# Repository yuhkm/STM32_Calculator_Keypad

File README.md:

# STM32_Calculator_Keypad
STM32 Based USB Keypad and Calculator Project  
<br>

## Overview
Development Period : 2024.08 ~ 2024.11
<br>
### HW
- MCU : STM32F401RET6  
- Displsy : ST7789 1.9" TFT LCD  
- Battery : Li-Po 500mAh 3.7V  
- Interface: USB (for keypad mode and charging)
- Switches: Cherry MX compatible mechanical switches  
  ( Kailh hot-swap sockets )
-  
-  
 
### SW
- Maximum expression length: 70 characters
- Calculator supported Operations  
  Basic arithmetic : +, -, ×, ÷  
  Parentheses : (), {}, []  
  Trigonometric functions : sin, cos, tan  
  Planned support for : asin, acos, atan, log, ln   
-  
-  

## Key Features
- Mode 0 : Calculator
- Mode 1 : USB Keypad  
<br>

| USB C | Power S/W | Mode S/W | Function            | Power source             |
|:-----:|:----------:|:--------:|--------------------|--------------------------|
|   0   |     0      |    X     | Power off          | -                        |
|   0   |     1      |    0     | Calculator mode    | Battery                  |
|   0   |     1      |    1     | -                  | -                        |
|   1   |     0      |    X     | Power off          | Battery charge           |
|   1   |     1      |    0     | Calculator mode    | USB + Battery charge     |
|   1   |     1      |    1     | USB Keypad mode    | USB + Battery charge     |

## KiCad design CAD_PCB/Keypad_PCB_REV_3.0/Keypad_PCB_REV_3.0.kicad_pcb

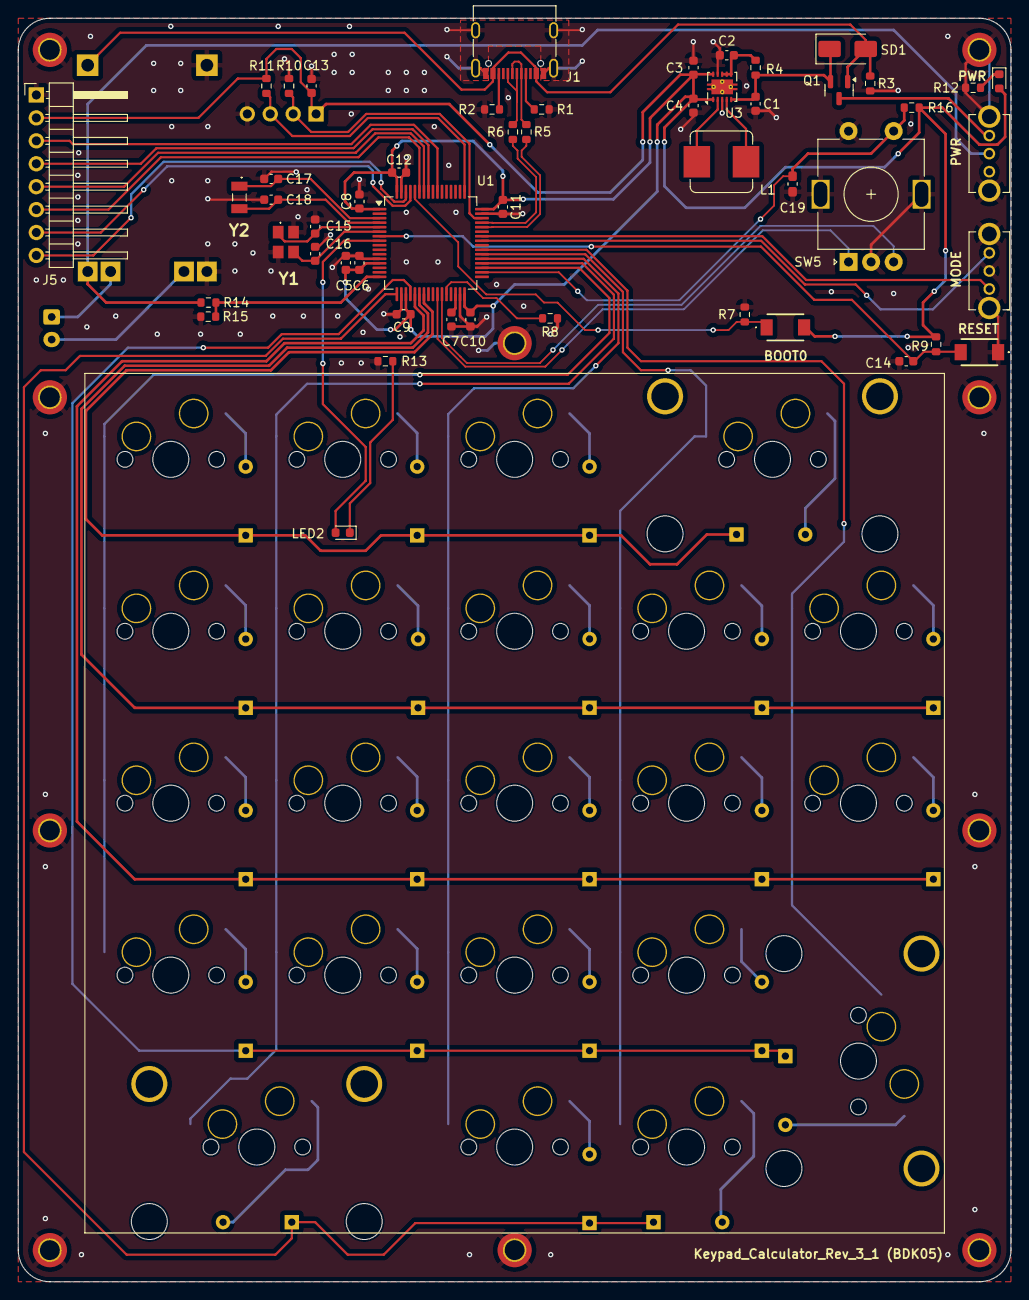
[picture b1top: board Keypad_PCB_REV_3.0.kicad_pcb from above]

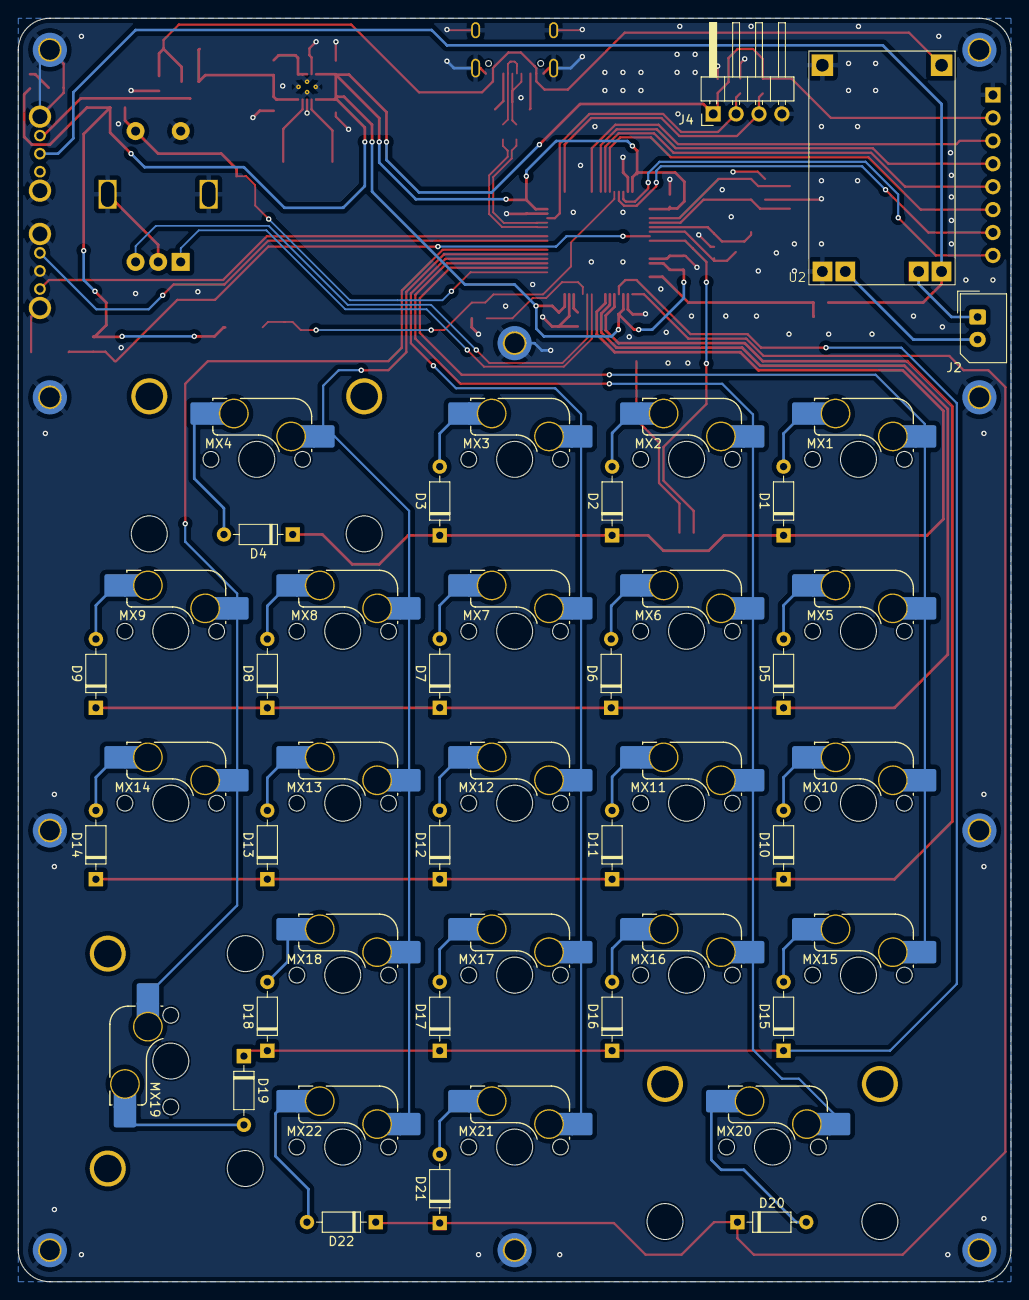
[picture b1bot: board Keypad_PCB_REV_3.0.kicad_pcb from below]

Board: 2 copper layers, 110.0 x 140.0 mm, 111 parts (47 on the bottom side), 74 nets.

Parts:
C1, C3, C4: 10uF(0603); C_0603_1608Metric
C2, C5, C9, C10, C11, C12, C13, C14: 100nF(0603); C_0603_1608Metric
C6, C8: 1uF(0603); C_0603_1608Metric
C7: 4.7uF(0603); C_0603_1608Metric
C15, C16: 18pF(0603); C_0603_1608Metric
C17, C18: 15pF(0603); C_0603_1608Metric
C19: NU(0603); C_0603_1608Metric_Pad1.08x0.95mm_HandSolder
D1, D2, D3, D4, D5, D6, D7, D8, D9, D10, D11, D12, D13, D14, D15, D16, D17, D18, D19, D20, D21, D22: 1N4148; D_DO-35_SOD27_P7.62mm_Horizontal
H1, H2, H3, H4, H5, H6, H7, H8, H9, H10: Pad; MountingHole_2.2mm_M2_DIN965_Pad_TopBottom
J1: USB_C_Receptacle_USB2.0_16P; USB_C_Receptacle_G-Switch_GT-USB-7010ASV
J2: Conn_01x02_Socket; Molex_SPOX_5267-02A_1x02_P2.50mm_Vertical
J4: Conn_01x04_Pin; PinHeader_1x04_P2.54mm_Horizontal
J5: Conn_01x08_Pin; PinHeader_1x08_P2.54mm_Horizontal
L1: 2.2uH; L_Bourns_SRP7028A_7.3x6.6mm
LED1, LED2: LED; LED_0603_1608Metric
MX1, MX2, MX3, MX4, MX5, MX6, MX7, MX8, MX9, MX10, MX11, MX12, MX13, MX14, MX15, MX16, MX17, MX18, MX19, MX20, MX21, MX22: MX_SW_HS; SW_MX_HS_CPG151101S11_1u
Q1: AO3401A; SOT-23
R1, R2: 5.1kR(0603); R_0603_1608Metric
R3, R7, R8, R9, R10, R11, R16: 10kR(0603); R_0603_1608Metric
R4: 100R(0603); R_0603_1608Metric
R5, R6: 22R(0603); R_0603_1608Metric
R12, R13: 1kR(0603); R_0603_1608Metric
R14: 30kR(0603); R_0603_1608Metric
R15: 7.5kR(0603); R_0603_1608Metric
SD1: SS14; D_SMA
ST9, ST19, ST20: MX_stab; STAB_MX_P_2u
SW1, SW2: SK-12D02-VG7; SK12D02VG7
SW3, SW4: TS-1088-AR02016; TS1088AR02016
SW5: RotaryEncoder_Switch_MP; RotaryEncoder_Alps_EC11E-Switch_Vertical_H20mm
U1: STM32F401RETx; LQFP-64_10x10mm_P0.5mm
U2: TP4056_Module
U3: TPS63001; Texas_DRC0010J_ThermalVias
Y1: X322525MOB4SI
Y2: Q13FC1350000400

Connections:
+3.3V: C3.1, C4.1, C5.1, C6.1, C8.1, C9.1, C10.1, C11.1, C12.1, C13.1, J4.1, J5.2, LED1.2 (A), R9.2, R11.1, R16.2, SW4.2 (NO), U1.1 (VBAT), U1.13 (VREF+), U1.19 (VDD), U1.32 (VDD), U1.48 (VDD), U1.64 (VDD), U3.1 (VOUT), U3.10 (FB)
/Stm32/D+: R6.1, U1.45 (PA12)
/Stm32/D-: R5.1, U1.44 (PA11)
BAT_ADC: R14.1, R15.2, U1.16 (PA2)
BLK: J5.8, U1.62 (PB9)
BOOT0: R7.1, SW4.1 (COM), U1.60 (BOOT0)
BOOT1: R8.1, U1.28 (PB2)
BOUT+: R14.2, SW1.2, U2.3 (Bout+)
COL0: MX1.1, MX5.1, MX10.1, MX15.1, U1.35 (PB14)
COL1: MX2.1, MX6.1, MX11.1, MX16.1, MX20.1, U1.36 (PB15)
COL2: MX3.1, MX7.1, MX12.1, MX17.1, MX21.1, U1.37 (PC6)
COL3: MX4.1, MX8.1, MX13.1, MX18.1, MX22.1, U1.38 (PC7)
COL4: MX9.1, MX14.1, MX19.1, U1.39 (PC8)
CS: J5.7, U1.61 (PB8)
DC: J5.6, U1.59 (PB7)
EXTI_0: SW5.A, U1.26 (PB0)
EXTI_2: SW5.B, U1.27 (PB1)
FN_LED: LED2.2 (A), U1.8 (PC0)
GND: C1.2, C2.2, C3.2, C4.2, C5.2, C6.2, C7.2, C8.2, C9.2, C10.2, C11.2, C12.2, C13.2, C14.2, C15.1, C16.2, C17.1, C18.1, C19.2, H1.1, H2.1, H3.1, H4.1, H5.1, H6.1, H7.1, H8.1, H9.1, H10.1, J1.A1 (GND), J1.A12 (GND), J1.B1 (GND), J1.B12 (GND), J1.S1 (SHIELD), J4.4, J5.1, R1.2, R2.2, R3.1, R7.2, R8.2, R10.1, R12.1, R13.1, R15.1, SW1.MH1, SW1.MH2, SW2.2, SW2.MH1, SW2.MH2, SW3.1 (COM), SW5.C, SW5.MP, SW5.S2, U1.12 (VSSA), U1.18 (VSS), U1.31 (VSS), U1.47 (VSS), U1.63 (VSS), U2.2 (In-), U2.6 (Bout-), U3.3 (PGND), U3.9 (GND), U3.11 (PGND), Y1.2 (GND_1), Y1.4 (GND_2)
NMODE_1: SW2.1, U1.42 (PA9)
NMODE_2: SW2.3, U1.41 (PA8)
NRST: C14.1, R9.1, SW3.2 (NO), U1.7 (NRST)
unnamed: D1.2 (A), MX1.2
unnamed: D2.2 (A), MX2.2
unnamed: D3.2 (A), MX3.2
unnamed: D4.2 (A), MX4.2
unnamed: D5.2 (A), MX5.2
unnamed: D6.2 (A), MX6.2
unnamed: D7.2 (A), MX7.2
unnamed: D8.2 (A), MX8.2
unnamed: D9.2 (A), MX9.2
unnamed: D10.2 (A), MX10.2
unnamed: D11.2 (A), MX11.2
unnamed: D12.2 (A), MX12.2
unnamed: D13.2 (A), MX13.2
unnamed: D14.2 (A), MX14.2
unnamed: D15.2 (A), MX15.2
unnamed: D16.2 (A), MX16.2
unnamed: D17.2 (A), MX17.2
unnamed: D18.2 (A), MX18.2
unnamed: D19.2 (A), MX19.2
unnamed: D20.2 (A), MX20.2
unnamed: D21.2 (A), MX21.2
unnamed: D22.2 (A), MX22.2
unnamed: J1.A5 (CC1), R1.1
unnamed: J1.B5 (CC2), R2.1
unnamed: J2.1, U2.4 (B+)
unnamed: J2.2, U2.5 (B-)
unnamed: LED1.1 (K), R12.2
unnamed: LED2.1 (K), R13.2
unnamed: Q1.3 (D), SW1.3
unnamed: C7.1, U1.30 (VCAP1)
unnamed: C2.1, R4.1, U3.6 (EN), U3.7 (PS/SYNC), U3.8 (VINA)
unnamed: L1.2, U3.4 (L1)
unnamed: L1.1, U3.2 (L2)
OCS32_IN: C17.2, U1.3 (PC14), Y2.1 (CRYSTAL)
OCS32_OUT: C18.2, U1.4 (PC15), Y2.2 (CRYSTAL)
OSCIN: C15.2, U1.5 (PH0), Y1.1 (CRYSTAL__1)
OSCOUT: C16.1, U1.6 (PH1), Y1.3 (CRYSTAL__2)
PA11_D-: J1.A7 (D-), J1.B7 (D-), R5.2
PA12_D+: J1.A6 (D+), J1.B6 (D+), R6.2
PWR+: C1.1, Q1.2 (S), R4.2, SD1.1 (K), U3.5 (VIN)
RES: J5.5, U1.58 (PB6)
ROW0: D1.1 (K), D2.1 (K), D3.1 (K), D4.1 (K), U1.23 (PA7)
ROW1: D5.1 (K), D6.1 (K), D7.1 (K), D8.1 (K), D9.1 (K), U1.22 (PA6)
ROW2: D10.1 (K), D11.1 (K), D12.1 (K), D13.1 (K), D14.1 (K), U1.21 (PA5)
ROW3: D15.1 (K), D16.1 (K), D17.1 (K), D18.1 (K), D19.1 (K), U1.20 (PA4)
ROW4: D20.1 (K), D21.1 (K), D22.1 (K), U1.17 (PA3)
Rotary_SW: C19.1, R16.1, SW5.S1, U1.34 (PB13)
SCL: J5.3, U1.55 (PB3)
SDA: J5.4, U1.57 (PB5)
SWCLK: J4.3, R11.2, U1.49 (PA14)
SWDIO: J4.2, R10.2, U1.46 (PA13)
USB+: J1.A4 (VBUS), J1.A9 (VBUS), J1.B4 (VBUS), J1.B9 (VBUS), Q1.1 (G), R3.2, SD1.2 (A), U2.1 (IN+)

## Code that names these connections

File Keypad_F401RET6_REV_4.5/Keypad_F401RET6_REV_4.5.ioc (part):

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Mcu.Name=STM32F401R(D-E)Tx
Mcu.Package=LQFP64
Mcu.UserName=STM32F401RETx
PA11.Mode=Device_Only
PA11.Signal=USB_OTG_FS_DM
PA12.Mode=Device_Only
PA12.Signal=USB_OTG_FS_DP
PA13.Mode=Serial_Wire
PA13.Signal=SYS_JTMS-SWDIO
PA14.Mode=Serial_Wire
PA14.Signal=SYS_JTCK-SWCLK
PA2.GPIOParameters=GPIO_Label
PA2.GPIO_Label=BAT_ADC
PA2.Signal=ADCx_IN2
PA3.GPIOParameters=GPIO_Label
PA3.GPIO_Label=COL4
PA3.Signal=GPIO_Output
PA4.GPIOParameters=GPIO_Label
PA4.GPIO_Label=COL3
PA4.Signal=GPIO_Output
PA5.GPIOParameters=GPIO_Label
PA5.GPIO_Label=COL2
PA5.Signal=GPIO_Output
PA6.GPIOParameters=GPIO_Label
PA6.GPIO_Label=COL1
PA6.Signal=GPIO_Output
PA7.GPIOParameters=GPIO_Label
PA7.GPIO_Label=COL0
PA7.Signal=GPIO_Output
PA8.GPIOParameters=GPIO_PuPd,GPIO_Label
PA8.GPIO_Label=NMODE_2
PA8.GPIO_PuPd=GPIO_PULLUP
PA8.Signal=GPIO_Input
PA9.GPIOParameters=GPIO_PuPd,GPIO_Label
PA9.GPIO_Label=NMODE_1
PA9.GPIO_PuPd=GPIO_PULLUP
PA9.Signal=GPIO_Input
PB14.GPIOParameters=GPIO_PuPd,GPIO_Label
PB14.GPIO_Label=ROW0
PB14.GPIO_PuPd=GPIO_PULLUP
PB14.Signal=GPIO_Input
PB15.GPIOParameters=GPIO_PuPd,GPIO_Label
PB15.GPIO_Label=ROW1
PB15.GPIO_PuPd=GPIO_PULLUP
PB15.Signal=GPIO_Input
PB3.Mode=Simplex_Bidirectional_Master
PB3.Signal=SPI1_SCK
PB5.Mode=Simplex_Bidirectional_Master
PB5.Signal=SPI1_MOSI
PB6.GPIOParameters=GPIO_Label
PB6.GPIO_Label=RES
PB6.Signal=GPIO_Output
PB7.GPIOParameters=GPIO_Label
PB7.GPIO_Label=DC
PB7.Signal=GPIO_Output
PB8.GPIOParameters=GPIO_Label
PB8.GPIO_Label=CS
PB8.Signal=GPIO_Output
PB9.GPIOParameters=GPIO_Label
PB9.GPIO_Label=BLK
PB9.Signal=GPIO_Output
PC0.GPIOParameters=GPIO_Label
PC0.GPIO_Label=Fn_LED
PC0.Signal=GPIO_Output
PC6.GPIOParameters=GPIO_PuPd,GPIO_Label
PC6.GPIO_Label=ROW2
PC6.GPIO_PuPd=GPIO_PULLUP
PC6.Signal=GPIO_Input
PC7.GPIOParameters=GPIO_PuPd,GPIO_Label
PC7.GPIO_Label=ROW3
PC7.GPIO_PuPd=GPIO_PULLUP
PC7.Signal=GPIO_Input
PC8.GPIOParameters=GPIO_PuPd,GPIO_Label
PC8.GPIO_Label=ROW4
PC8.GPIO_PuPd=GPIO_PULLUP
PC8.Signal=GPIO_Input
PH0\ -\ OSC_IN.Mode=HSE-External-Oscillator
PH0\ -\ OSC_IN.Signal=RCC_OSC_IN
PH1\ -\ OSC_OUT.Mode=HSE-External-Oscillator
PH1\ -\ OSC_OUT.Signal=RCC_OSC_OUT
RCC.HSE_VALUE=25000000
RCC.SYSCLKFreq_VALUE=84000000
RCC.SYSCLKSource=RCC_SYSCLKSOURCE_PLLCLK
board=custom

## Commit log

2025-08-01 Add cad files
2025-08-01 Add STM32 files0
